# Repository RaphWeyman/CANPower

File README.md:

# CANPower
Accessory power controller for BMW CAN bus bikes

Two channel power switch using BMW CAN bus messages to control switch output.
Microchip PIC24 based.

Hardware is a printed circuit board created and modifiable with KiCAD. If no modifications are required then the gerbers zip file
can be used as is to get manufactured. The gerber file names are as required by Elecrow.

The software is packaged as a Microchip PIC IDE project and requires Microchip MPLAB X with the 16 bit PIC compiler installed - all free
from the Microchip website.

The 6 way "debug" header on the PCB connects directly to the the Microchip PICKit 3 debugger/programmer. This or some other programmer is
required in order to program the software to the Microchip MCU.

Functionality may easily be changed by modifying the application.c file.
Here's what the default application does:-
 * Switch channel 1 is set to go fully on or fully off with the ignition for accessory power
 * (can easily be changed to staying off by changing the CHANNEL_1_ON define).
 * 
 * Channel 0 is controlled by the ASC switch (can be changed with the BUTTON_PRESSED define).
 * Channel 0 has two modes; modulated and unmodulated. Unmodulated behaves like channel 1; fully on
 * or fully off with the ignition.
 * Modulated is PWM controlled for several power levels from fully off to fully on and each of the quarters
 * inbetween (modify at the CHANNEL_0_PWM_SETTING). PWM is slow for heated clothing but can be changed to
 * fast by changing the CHANNEL_0_PWM_MODE.
 * A long press (>20 seconds) of the control button toggles between modulated and unmodulated modes.
 * A short press (<1 second) of the control button while in modulated mode cycles through the modulation levels.
 * Channel 0 mode and modulation level are stored in EEPROM at power off time (immmediately prior to transition to the
 * alarm simulation state)).
 * 
 * An alarm simulation is included after the ignition is turned off (and the POWER_OFF_DELAY has elapsed).
 * During alarm simulation the switch chip is turned off but the LED indicates as if there were an
 * alarm module armed.
 * Alarm simulation continues for the ALARM_SIMULATION_TIME or can be disabled by setting the ALARM_SIMULATION_TIME to zero.
 * A kickstand warning indication is output to the LEDs if the kickstand is deployed while the ignition is on
 * The warning can be disabled by commenting out the KICKSTAND_WARNING define.
 * 
 * Ignition on is determined by CAN messages being received.
 * Fully on state is maintained POWER_OFF_DELAY. If no CAN messages are received for longer than the POWER_OFF_DELAY
 * then channels 0 and 1 are both turned off and the alarm simulation is stated.
 * Power to the CPU is latched using the PORT_POWER hardware control. When either the ignition is on or the PORT_POWER is set to
 * POWER_PORT_ON power is supplied to the CPU. This allows the CPU to maintain power during the POWER_OFF_DELAY
 * and the ALARM_SIMLATION_TIME. At the end of the ALARM_SIMULATION_TIME, the PORT_POWER is set to POWER_PORT_OFF so as to cut
 * power.
 * 
 * Indications are assumed to be for a single bi-colour LED.
 * LED is dimmed according to the ambient light sensor CAN bus message.
 * LED0 fully on indicates channel 0 is in unmodulated mode.
 * LED1 on but with between 1 and 4 inverse blips indicates channel 0 modulated mode and the number of inverse blips indicate
 * the modulation level (4 blips - fully on).
 * LED1 flashes 4 blips when the channel 0 mode is changed.
 * Both LED0 and LED1 fully off indicate either modulated mode with channel 0 output at the fully off level or no power to the CPU.
 * LED0 flashing at 1Hz indicates that the kickstand is extended.
 * LED0 flashing at 4Hz indicates a switch chip fault - recover by ignition off/ignition on.
 * LED1 blips every few seconds for the alarm simulation.
 * Indications can all be changed by modifying the INDICATIONS and CHANNEL_0_INDICATIONS table.
 *
 * Application is a state machine with a single state variable 'state' and a function of type
 * state_function_t for each state.
 * Each state function must implement the actions for state entry and for state maintenance.
 * The current state's function is invoked regularly (once per timer tick).
 * The StateTransition function is used to change state.
 * The state machnine can be extended by adding to BOTH the states_t and the STATE_FUNCTIONS

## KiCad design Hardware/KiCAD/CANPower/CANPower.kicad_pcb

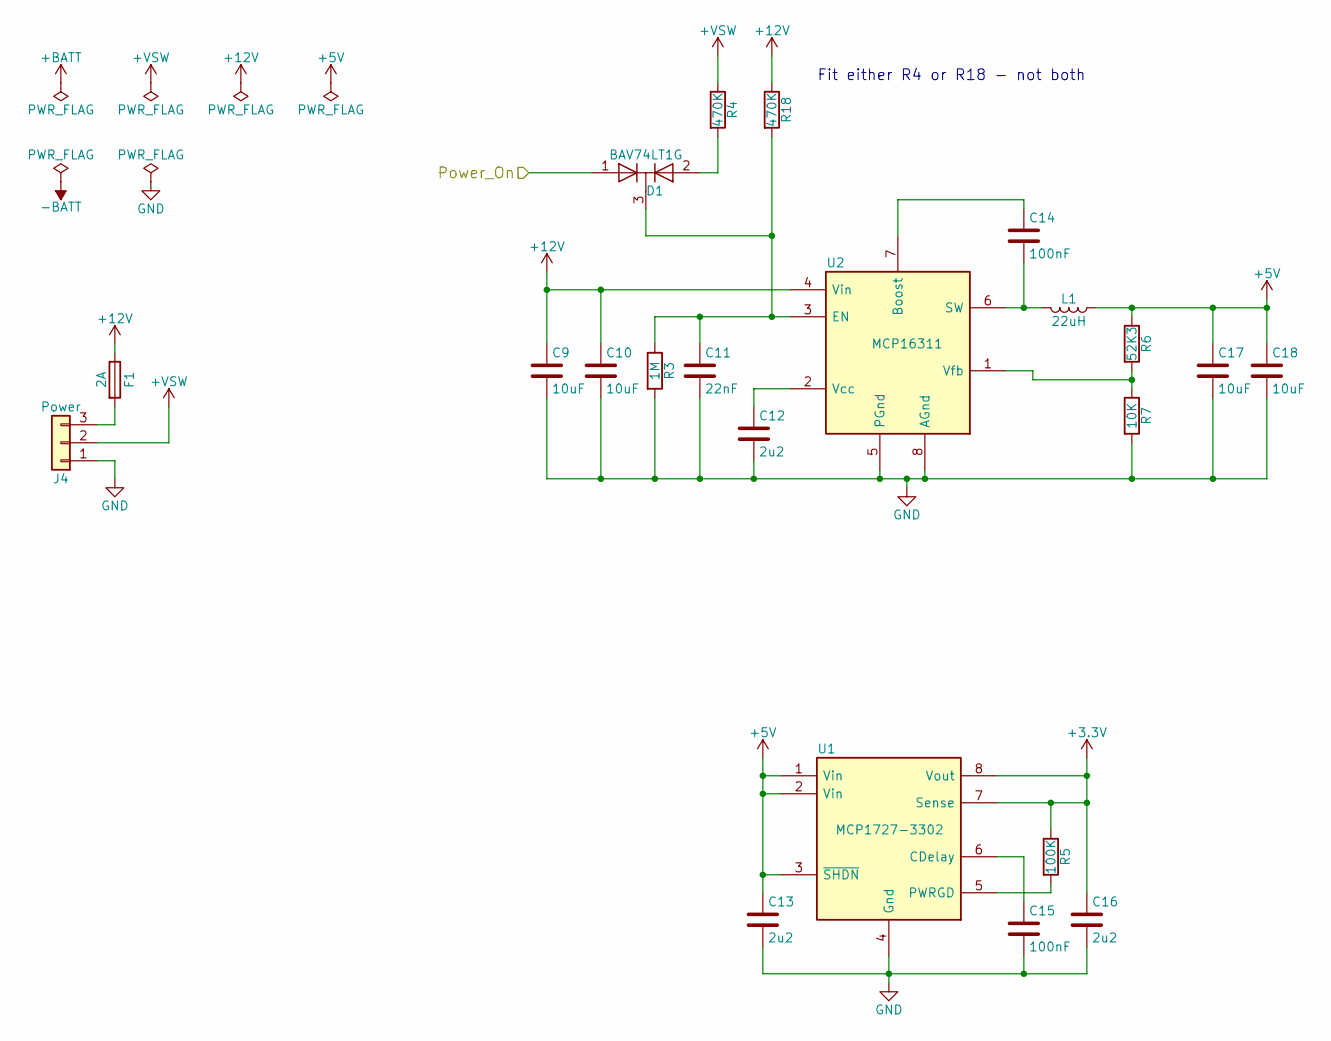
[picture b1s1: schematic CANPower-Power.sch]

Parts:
C9, C10, C17, C18: 10uF; C_1210
C11: 22nF; C_1206
C12, C13, C16: 2u2; C_1210
C14, C15: 100nF; C_1206
D1: BAV74LT1G; SOT-23
F1: 2A; R_1206
J4: Power; Pin_Header_Straight_1x03_Pitch2.54mm
L1: 22uH; Coilcraft_MSS7341
R3: 1M; R_1206
R4, R18: 470K; R_1206
R5: 100K; R_1206
R6: 52K3; R_1206
R7: 10K; R_1206
U1: MCP1727-3302; SOIC-8_3.9x4.9mm_Pitch1.27mm
U2: MCP16311; MSOP-8_3x3mm_Pitch0.65mm

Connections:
+3V3: C16.1, R5.1, U1.7 (Sense), U1.8 (Vout); also elsewhere on the board
+5V: C13.1, C17.1, C18.1, L1.1, R6.1, U1.1 (Vin), U1.2 (Vin), U1.3 (~SHDN~); also elsewhere on the board
+12V: C9.1, C10.1, F1.1, R18.1, U2.4 (Vin)
+VSW: J4.2, R4.1
/CPU/Power_On: D1.1 (A); also elsewhere on the board
GND: C9.2, C10.2, C11.2, C12.2, C13.2, C15.2, C16.2, C17.2, C18.2, J4.1, R3.2, R7.2, U1.4 (Gnd), U2.5 (PGnd), U2.8 (AGnd); also elsewhere on the board
unnamed: C11.1, D1.3 (K), R3.1, R18.2, U2.3 (EN)
unnamed: C12.1, U2.2 (Vcc)
unnamed: C14.1, U2.7 (Boost)
unnamed: C14.2, L1.2, U2.6 (SW)
unnamed: C15.1, U1.6 (CDelay)
unnamed: D1.2 (A), R4.2
unnamed: F1.2, J4.3
unnamed: R5.2, U1.5 (PWRGD)
unnamed: R6.2, R7.1, U2.1 (Vfb)

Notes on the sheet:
Fit either R4 or R18 - not both

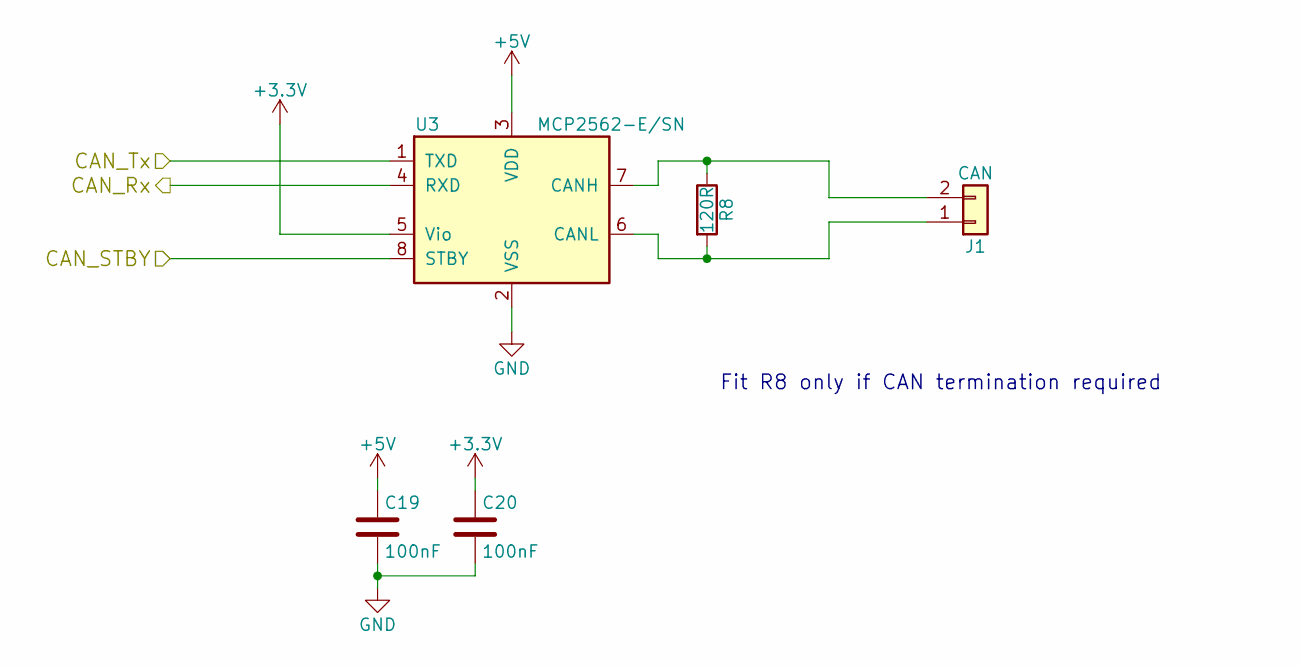
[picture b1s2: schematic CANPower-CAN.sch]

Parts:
C19, C20: 100nF; C_1206
J1: CAN; Pin_Header_Straight_1x02_Pitch2.54mm
R8: 120R; R_1206
U3: MCP2562-E/SN; SOIC-8_3.9x4.9mm_Pitch1.27mm

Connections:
+3V3: C20.1, U3.5 (Vio); also elsewhere on the board
+5V: C19.1, U3.3 (VDD); also elsewhere on the board
/CAN/CAN_Rx: U3.4 (RXD); also elsewhere on the board
/CAN/CAN_STBY: U3.8 (STBY); also elsewhere on the board
/CAN/CAN_Tx: U3.1 (TXD); also elsewhere on the board
GND: C19.2, C20.2, U3.2 (VSS); also elsewhere on the board
unnamed: J1.1, R8.2, U3.6 (CANL)
unnamed: J1.2, R8.1, U3.7 (CANH)

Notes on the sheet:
Fit R8 only if CAN termination required

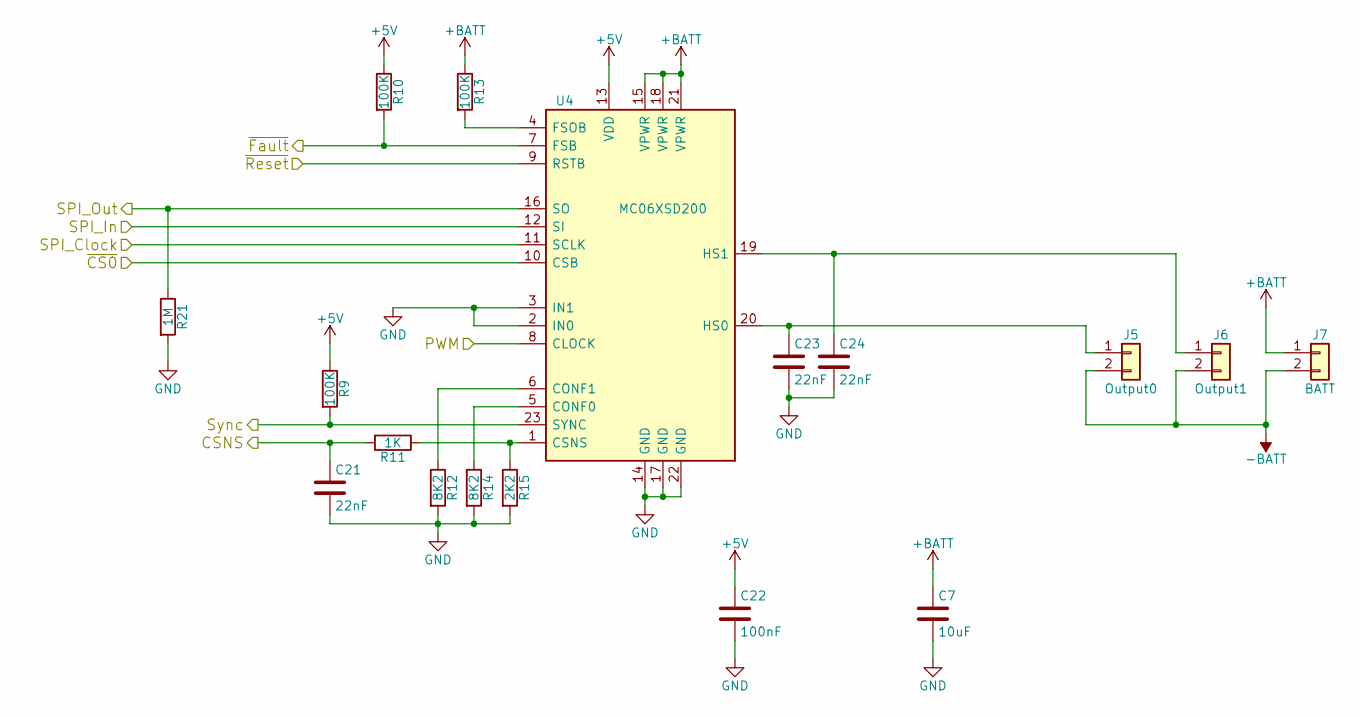
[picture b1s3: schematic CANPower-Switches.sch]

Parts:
C7: 10uF; C_1210
C21, C23, C24: 22nF; C_1206
C22: 100nF; C_1206
J5: Output0; WireConnection_1.50mmDrill
J6: Output1; WireConnection_1.50mmDrill
J7: BATT; WireConnection_1.50mmDrill
R9, R10, R13: 100K; R_1206
R11: 1K; R_1206
R12, R14: 8K2; R_1206
R15: 2K2; R_1206
R21: 1M; R_1206
U4: MC06XSD200; QFN-23_12x12mm_Pitch0.9mm_holes

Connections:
+5V: C22.1, R9.1, R10.1, U4.13 (VDD); also elsewhere on the board
+BATT: C7.1, J7.1, R13.1, U4.15 (VPWR), U4.18 (VPWR), U4.21 (VPWR)
-BATT: J5.2, J6.2, J7.2
/CPU/CSNS: C21.1, R11.2; also elsewhere on the board
/CPU/Output_Wake: U4.9 (RSTB); also elsewhere on the board
/CPU/PWM: U4.8 (CLOCK); also elsewhere on the board
/CPU/SPI_Clock: U4.11 (SCLK); also elsewhere on the board
/CPU/SPI_In: R21.1, U4.16 (SO); also elsewhere on the board
/CPU/Sync: R9.2, U4.23 (SYNC); also elsewhere on the board
/CPU/~CS0~: U4.10 (CSB); also elsewhere on the board
/CPU/~Fault~: R10.2, U4.7 (FSB); also elsewhere on the board
/Switches/SPI_In: U4.12 (SI); also elsewhere on the board
GND: C7.2, C21.2, C22.2, C23.2, C24.2, R12.2, R14.2, R15.2, R21.2, U4.2 (IN0), U4.3 (IN1), U4.14 (GND), U4.17 (GND), U4.22 (GND); also elsewhere on the board
unnamed: C23.1, J5.1, U4.20 (HS0)
unnamed: C24.1, J6.1, U4.19 (HS1)
unnamed: R11.1, R15.1, U4.1 (CSNS)
unnamed: R12.1, U4.6 (CONF1)
unnamed: R13.2, U4.4 (FSOB)
unnamed: R14.1, U4.5 (CONF0)

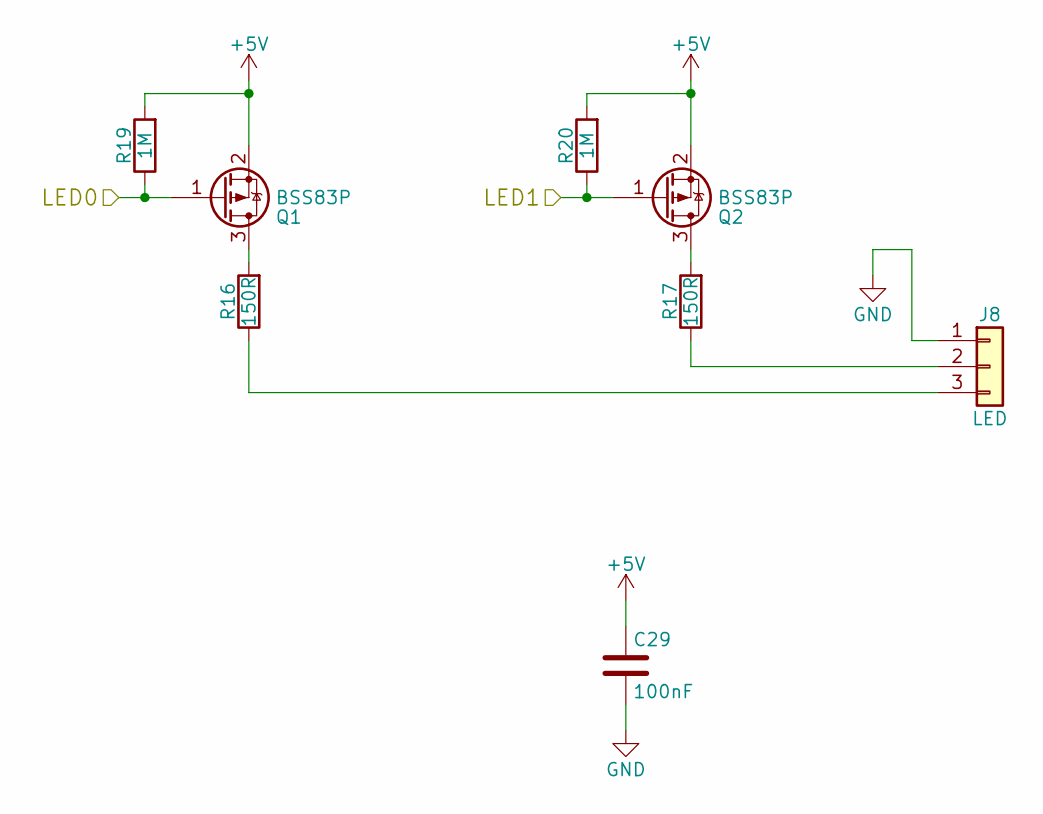
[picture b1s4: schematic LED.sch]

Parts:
C29: 100nF; C_1206
J8: LED; Pin_Header_Straight_1x03_Pitch2.54mm
Q1, Q2: BSS83P; SOT-23
R16, R17: 150R; R_1206
R19, R20: 1M; R_1206

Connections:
+5V: C29.1, Q1.2 (S), Q2.2 (S), R19.2, R20.2; also elsewhere on the board
/CPU/LED0: Q1.1 (G), R19.1; also elsewhere on the board
/CPU/LED1: Q2.1 (G), R20.1; also elsewhere on the board
GND: C29.2, J8.1; also elsewhere on the board
unnamed: J8.2, R17.1
unnamed: J8.3, R16.1
unnamed: Q1.3 (D), R16.2
unnamed: Q2.3 (D), R17.2

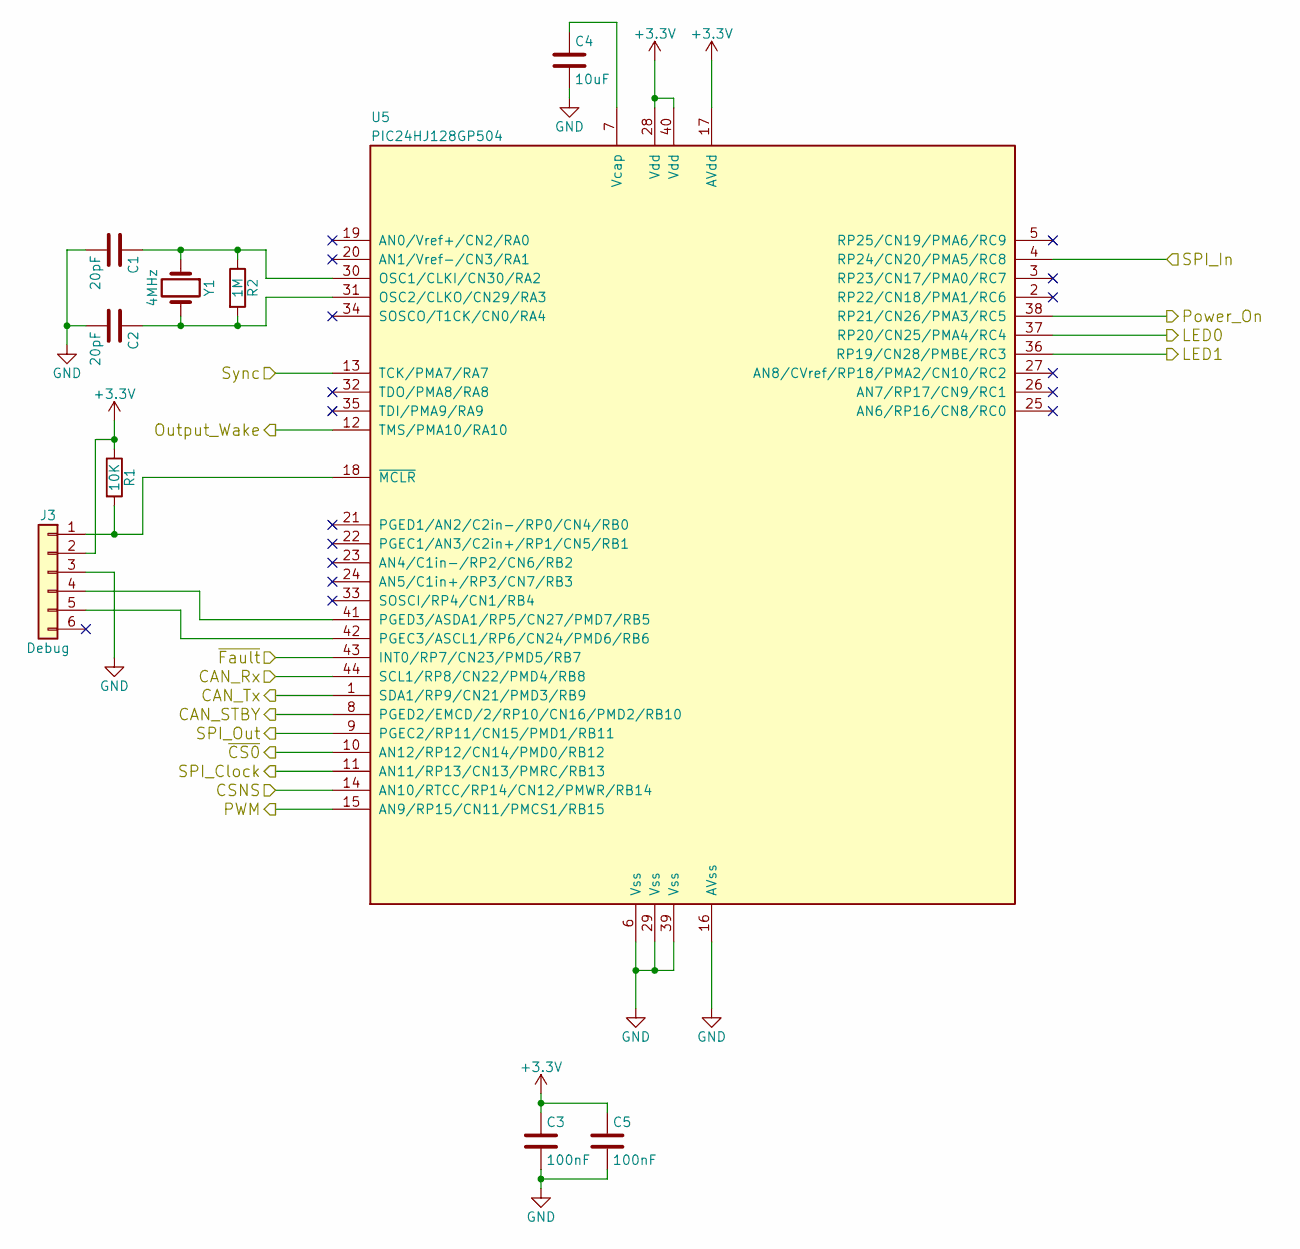
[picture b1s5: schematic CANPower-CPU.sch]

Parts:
C1, C2: 20pF; C_1206
C3, C5: 100nF; C_1206
C4: 10uF; C_1210
J3: Debug; Pin_Header_Straight_1x06_Pitch2.54mm
R1: 10K; R_1206
R2: 1M; R_1206
U5: PIC24HJ128GP504; PQFP-44_10x10mm_Pitch0.8mm
Y1: 4MHz; Crystal_SMD_HC49-SD

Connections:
+3V3: C3.1, C5.1, J3.2, R1.1, U5.17 (AVdd), U5.28 (Vdd), U5.40 (Vdd); also elsewhere on the board
/CAN/CAN_Rx: U5.44 (SCL1/RP8/CN22/PMD4/RB8); also elsewhere on the board
/CAN/CAN_STBY: U5.8 (PGED2/EMCD/2/RP10/CN16/PMD2/RB10); also elsewhere on the board
/CAN/CAN_Tx: U5.1 (SDA1/RP9/CN21/PMD3/RB9); also elsewhere on the board
/CPU/CSNS: U5.14 (AN10/RTCC/RP14/CN12/PMWR/RB14); also elsewhere on the board
/CPU/LED0: U5.37 (RP20/CN25/PMA4/RC4); also elsewhere on the board
/CPU/LED1: U5.36 (RP19/CN28/PMBE/RC3); also elsewhere on the board
/CPU/Output_Wake: U5.12 (TMS/PMA10/RA10); also elsewhere on the board
/CPU/PWM: U5.15 (AN9/RP15/CN11/PMCS1/RB15); also elsewhere on the board
/CPU/Power_On: U5.38 (RP21/CN26/PMA3/RC5); also elsewhere on the board
/CPU/SPI_Clock: U5.11 (AN11/RP13/CN13/PMRC/RB13); also elsewhere on the board
/CPU/SPI_In: U5.4 (RP24/CN20/PMA5/RC8); also elsewhere on the board
/CPU/Sync: U5.13 (TCK/PMA7/RA7); also elsewhere on the board
/CPU/~CS0~: U5.10 (AN12/RP12/CN14/PMD0/RB12); also elsewhere on the board
/CPU/~Fault~: U5.43 (INT0/RP7/CN23/PMD5/RB7); also elsewhere on the board
/Switches/SPI_In: U5.9 (PGEC2/RP11/CN15/PMD1/RB11); also elsewhere on the board
GND: C1.2, C2.2, C3.2, C4.2, C5.2, J3.3, U5.6 (Vss), U5.16 (AVss), U5.29 (Vss), U5.39 (Vss); also elsewhere on the board
unnamed: C1.1, R2.1, U5.30 (OSC1/CLKI/CN30/RA2), Y1.1
unnamed: C2.1, R2.2, U5.31 (OSC2/CLKO/CN29/RA3), Y1.2
unnamed: C4.1, U5.7 (Vcap)
unnamed: J3.1, R1.2, U5.18 (~MCLR~)
unnamed: J3.4, U5.41 (PGED3/ASDA1/RP5/CN27/PMD7/RB5)
unnamed: J3.5, U5.42 (PGEC3/ASCL1/RP6/CN24/PMD6/RB6)

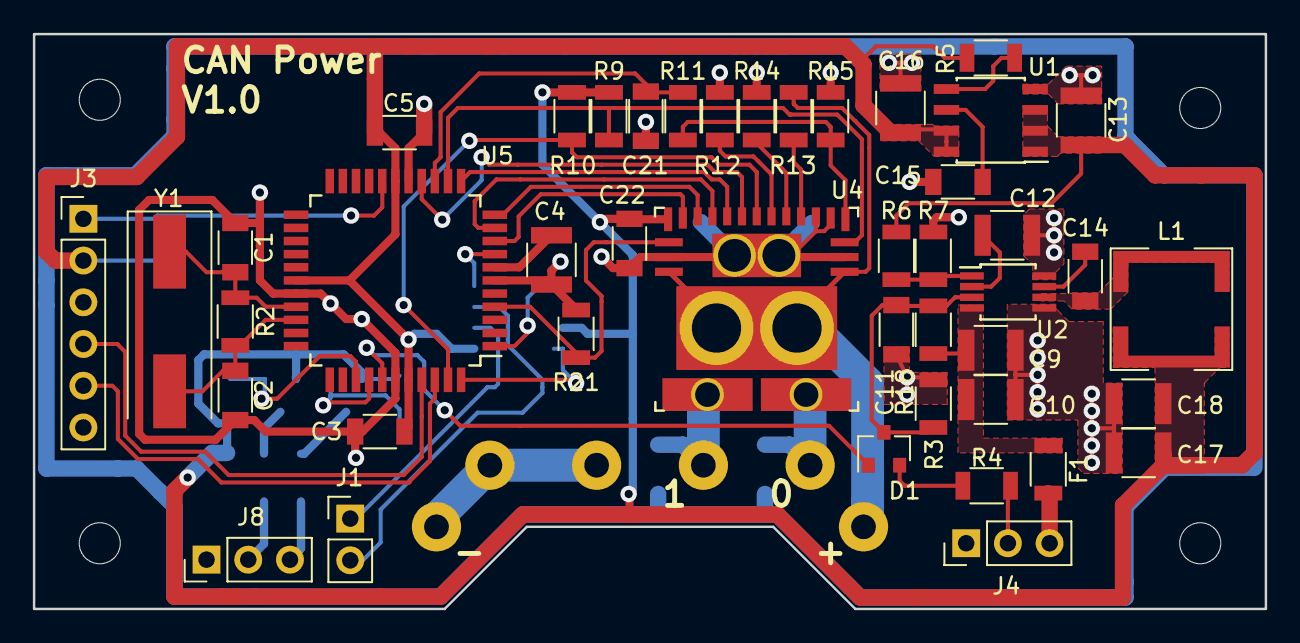
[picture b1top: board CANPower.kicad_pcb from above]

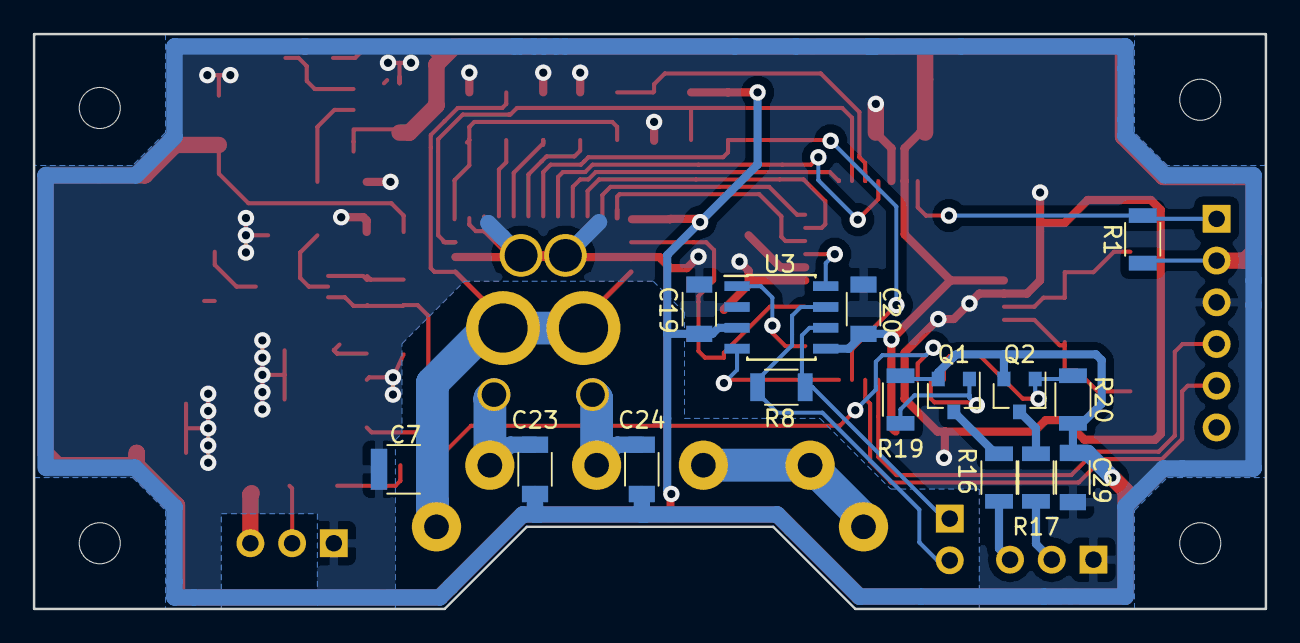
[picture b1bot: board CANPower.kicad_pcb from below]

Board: 2 copper layers, 75.0 x 35.0 mm, 62 parts (15 on the bottom side), 49 nets.
